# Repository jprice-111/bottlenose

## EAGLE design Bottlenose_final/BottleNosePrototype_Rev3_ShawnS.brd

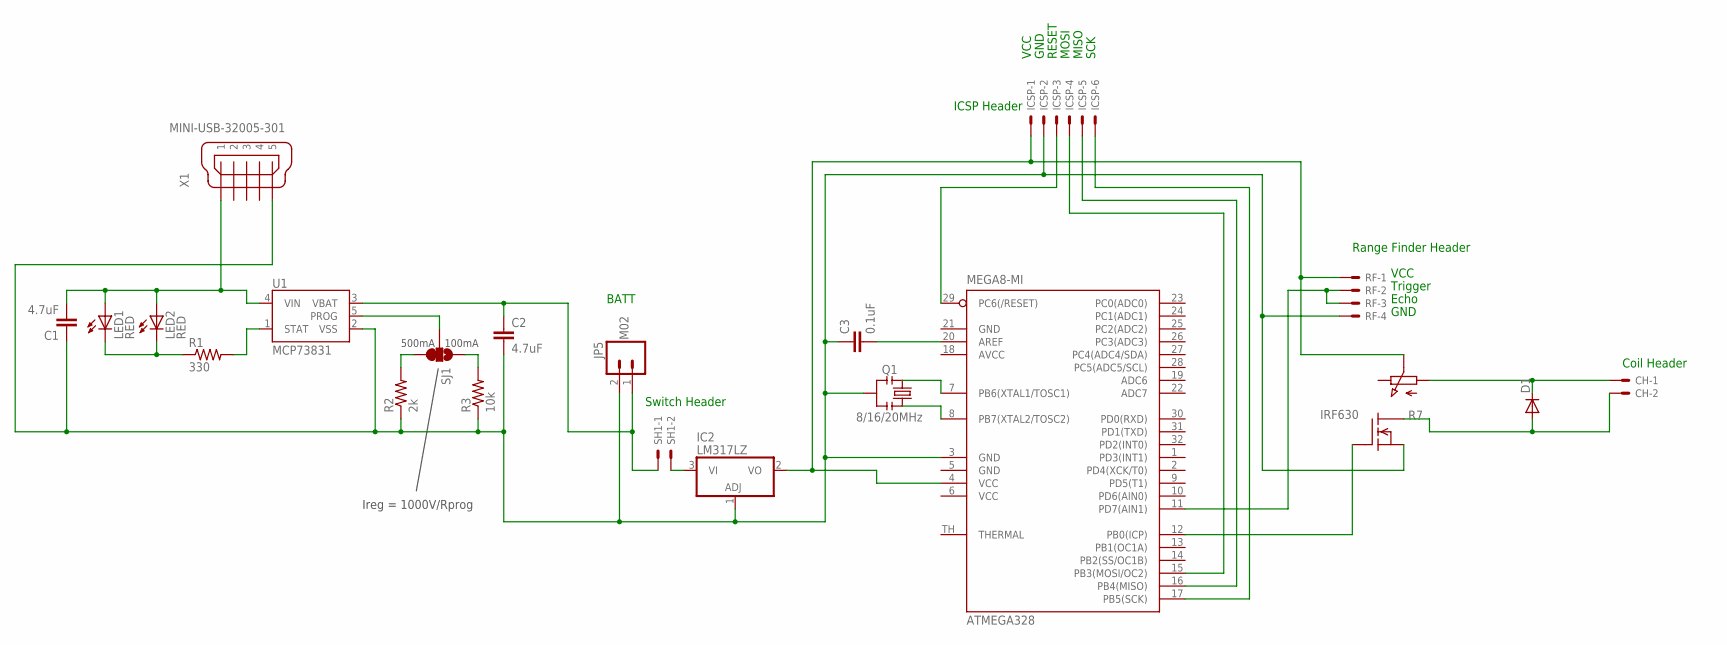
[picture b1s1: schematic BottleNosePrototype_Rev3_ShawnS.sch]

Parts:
ATMEGA328: MEGA8-MI; MLF32-TH; MPN ATMEGA88PA-MU
C1, C2: 4.7uF; 0402-CAP
C3: 0.1uF; 0402-CAP
CH: 22-23-2021
D1: DIODE-MICROMELF-R; MICROMELF-R
IC2: LM317LZ; TO92
ICSP: 22-23-2061
IRF630: IRF620; TO220
JP5: M02; 1X02
LED1, LED2: RED; LED-0603
Q1: 8/16/20MHz; RESONATOR-SMD
R1: 330; 0402-RES
R2: 2k; 0402-RES
R3: 10k; 0402-RES
R7: PC25
RF: 22-23-2041
SH1: 22-23-2021
SJ1: SOLDERJUMPER_2WAYS; SJ_3
U1: MCP73831; SOT23-5
X1: MINI-USB-32005-301; 32005-301

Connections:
AREF: ATMEGA328.20 (AREF), C3.2
AVCC: ATMEGA328.18 (AVCC)
GND: ATMEGA328.5 (GND), ATMEGA328.21 (GND)
unnamed: ATMEGA328.12 (PB0(ICP)), IRF630.1 (G)
unnamed: R1.2, U1.1 (STAT)
unnamed: LED1.C, LED2.C, R1.1
unnamed: R2.2, SJ1.3
unnamed: IC2.3 (VI), SH1.2
unnamed: CH.2, D1.A, IRF630.2 (D)
unnamed: R3.2, SJ1.1
unnamed: ATMEGA328.7 (PB6(XTAL1/TOSC1)), Q1.3
unnamed: ATMEGA328.8 (PB7(XTAL2/TOSC2)), Q1.1
unnamed: CH.1, D1.C, R7.A
unnamed: ATMEGA328.15 (PB3(MOSI/OC2)), ICSP.4
unnamed: ATMEGA328.17 (PB5(SCK)), ICSP.6
unnamed: ATMEGA328.16 (PB4(MISO)), ICSP.5
unnamed: ATMEGA328.29 (PC6(/RESET)), ICSP.3
unnamed: C1.2, LED1.A, LED2.A, U1.4 (VIN), X1.1
unnamed: C2.1, JP5.1, SH1.1, U1.3 (VBAT)
unnamed: ATMEGA328.3 (GND), C1.1, C2.2, C3.1, IC2.1 (ADJ), ICSP.2, IRF630.3 (S), JP5.2, Q1.2, R2.1, R3.1, RF.4, U1.2 (VSS), X1.5
unnamed: ATMEGA328.4 (VCC), IC2.2 (VO), ICSP.1, R7.S, RF.1
unnamed: ATMEGA328.11 (PD7(AIN1)), RF.2, RF.3
PROG: SJ1.2, U1.5 (PROG)
VCC: ATMEGA328.6 (VCC)

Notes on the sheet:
500mA
100mA
Ireg = 1000V/Rprog
VCC
Trigger
Echo
GND
Range Finder Header
Coil Header
Switch Header
RESET
MOSI
MISO
SCK
ICSP Header
BATT

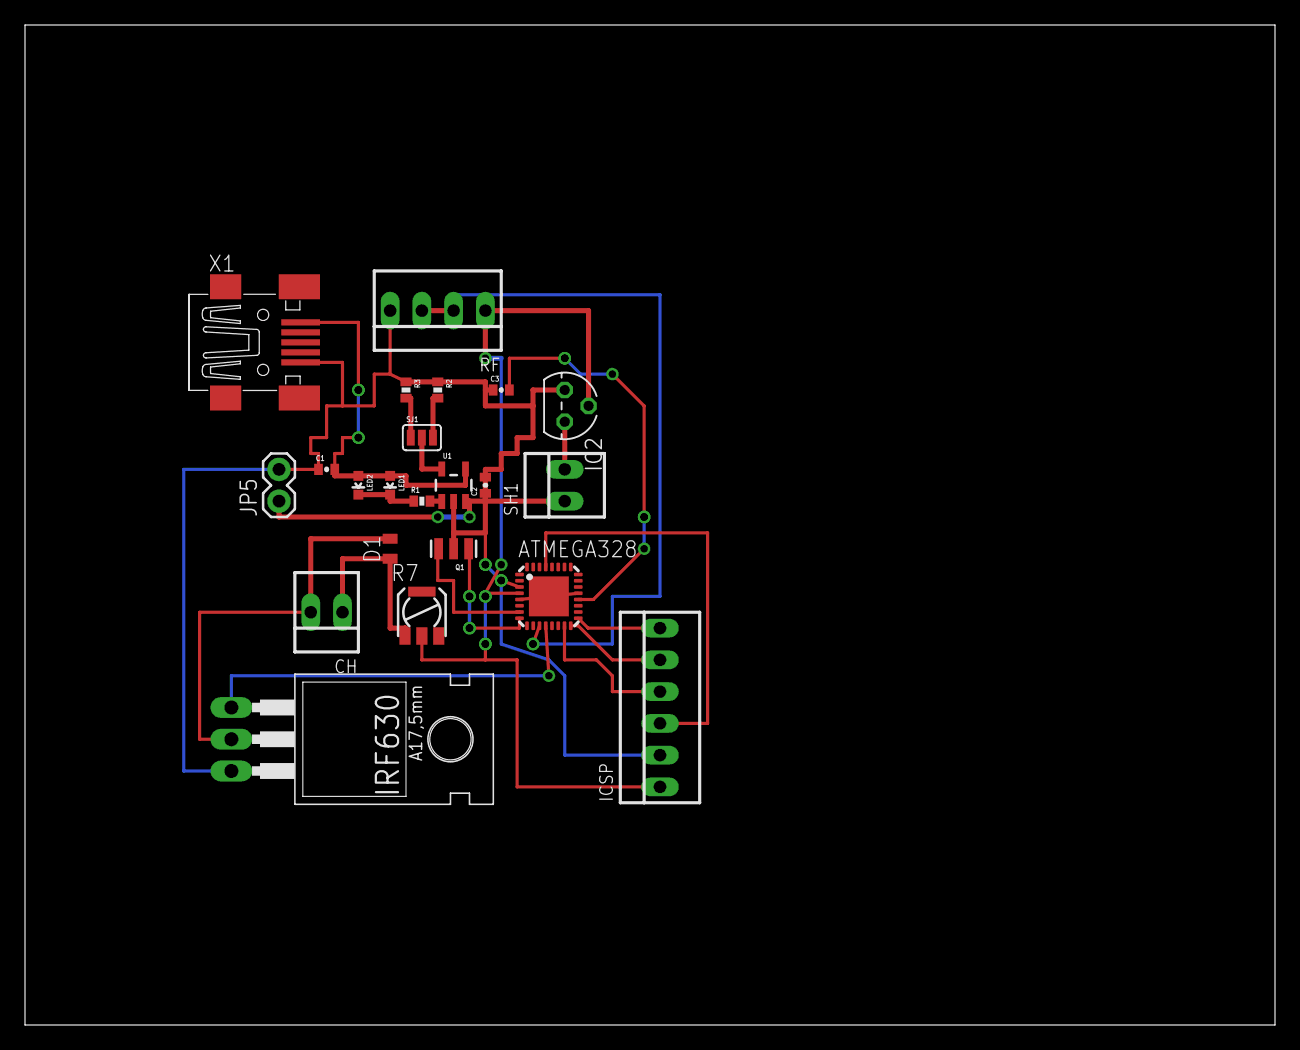
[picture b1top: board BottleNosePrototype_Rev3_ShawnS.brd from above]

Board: 2 copper layers, 100.0 x 80.0 mm, 22 parts (0 on the bottom side), 22 nets.

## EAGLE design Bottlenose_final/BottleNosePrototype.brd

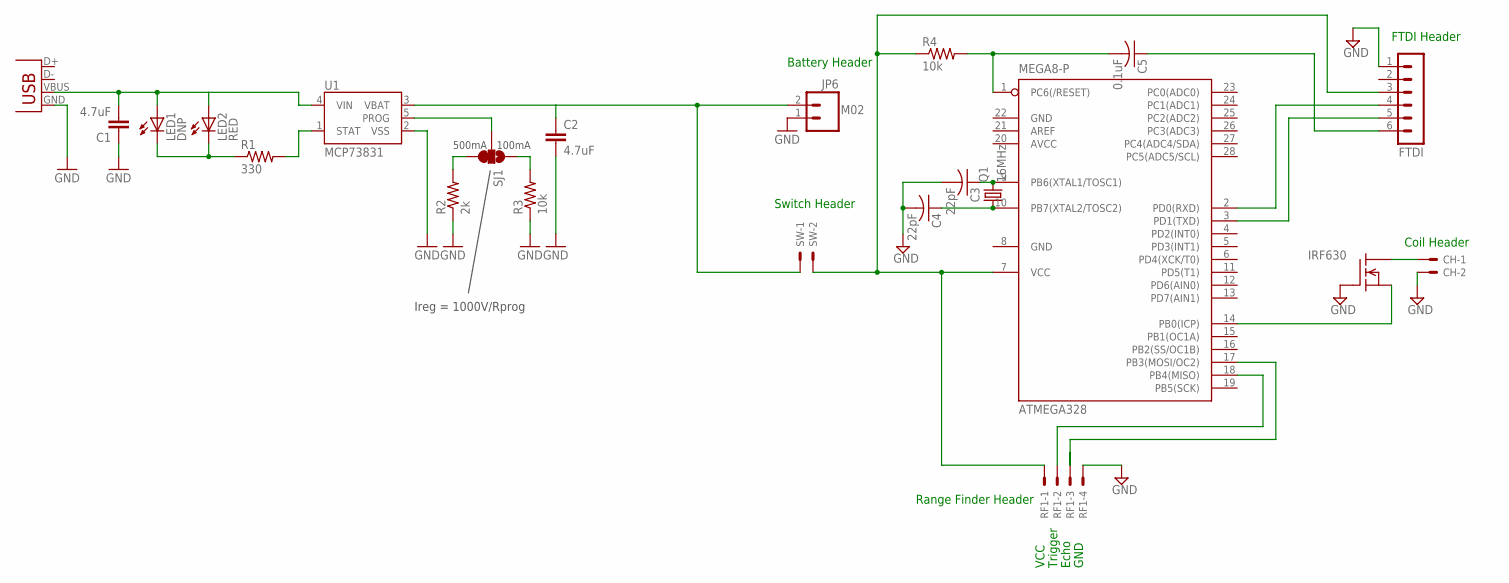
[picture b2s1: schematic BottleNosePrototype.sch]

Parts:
ATMEGA328: MEGA8-P; DIL28-3
C1, C2: 4.7uF; 0402-CAP
C3, C4: 22pF; C025-024X044
C5: 0.1uF; C025-024X044
CH: 22-23-2021
FTDI: MA06-1
IRF630: IRF620; TO220
JP6: M02; 1X02
LED1: DNP; LED3MM
LED2: RED; LED-0603
Q1: 16MHz; TC26V
R1: 330; 0402-RES
R2: 2k; 0402-RES
R3: 10k; 0402-RES
R4: 10k; 0204/5
RF1: 22-23-2041
SJ1: SOLDERJUMPER_2WAYS; SJ_3
SW: 22-23-2021
U1: MCP73831; SOT23-5
X2: USBSMD; USB-MINIB

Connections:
AVCC: ATMEGA328.20 (AVCC)
GND: ATMEGA328.8 (GND), ATMEGA328.22 (GND), C1.1, C2.2, C3.2, C4.2, CH.2, FTDI.1, IRF630.1 (G), JP6.1, R2.1, R3.1, RF1.4, U1.2 (VSS), X2.GND
unnamed: R1.2, U1.1 (STAT)
unnamed: LED1.K (C), LED2.C, R1.1
unnamed: R2.2, SJ1.3
unnamed: ATMEGA328.7 (VCC), FTDI.3, R4.1, RF1.1, SW.2
unnamed: C2.1, JP6.2, SW.1, U1.3 (VBAT)
unnamed: R3.2, SJ1.1
unnamed: ATMEGA328.9 (PB6(XTAL1/TOSC1)), C3.1, Q1.2
unnamed: ATMEGA328.18 (PB4(MISO)), RF1.2
unnamed: ATMEGA328.14 (PB0(ICP)), IRF630.3 (S)
unnamed: CH.1, IRF630.2 (D)
unnamed: ATMEGA328.10 (PB7(XTAL2/TOSC2)), C4.1, Q1.1
unnamed: ATMEGA328.17 (PB3(MOSI/OC2)), RF1.3
unnamed: ATMEGA328.2 (PD0(RXD)), FTDI.4
unnamed: ATMEGA328.3 (PD1(TXD)), FTDI.5
unnamed: C5.1, FTDI.6
unnamed: ATMEGA328.1 (PC6(/RESET)), C5.2, R4.2
unnamed: C1.2, LED1.A, LED2.A, U1.4 (VIN), X2.VBUS
PROG: SJ1.2, U1.5 (PROG)

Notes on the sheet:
500mA
100mA
Ireg = 1000V/Rprog
Range Finder Header
Coil Header
VCC
Trigger
Echo
GND
Switch Header
Battery Header
FTDI Header

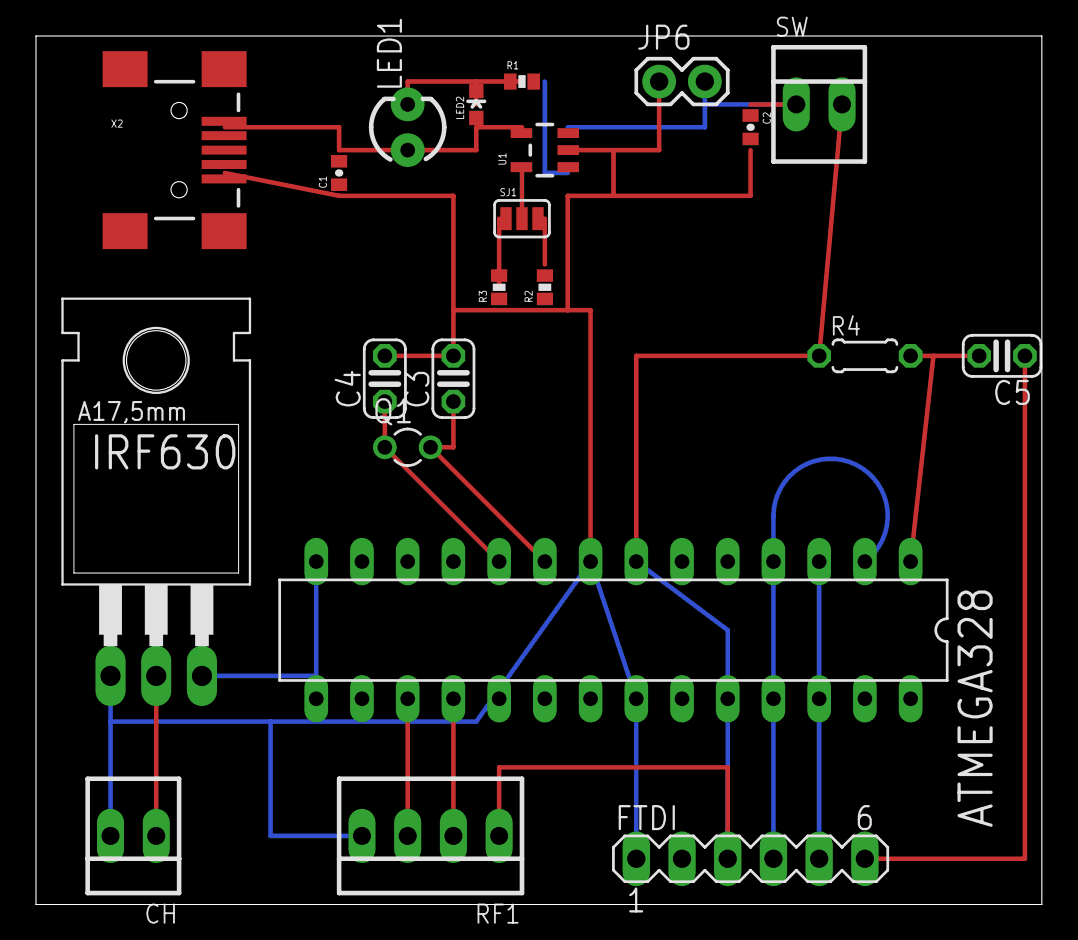
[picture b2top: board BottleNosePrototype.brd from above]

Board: 2 copper layers, 55.9 x 48.2 mm, 22 parts (0 on the bottom side), 19 nets.

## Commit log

2013-02-01 by Marlo, 1/2/2013, to incorporate thermosensor.
2013-03-18 Mike's current code
2013-03-18 libraries
2013-03-31 using this to make a directory.
2013-03-31 A custom eagle library containing the battery charger IC and the thermosensor.
2013-03-31 An updated copy of the bottlenose eagle schematic.
2013-03-31 An updated copy of the bottlenose arduino sketch. Shouldn't suffer from lag, notify me if it does. Relies on an external switch to change between sensors (pin 9 or pin 10 high).
2013-03-31 Pictures of a mock setup of an electromagnet. Not sure if it's the best possible way, but this is how I imagined it.
2013-03-31 Parts list. Content will end up in the google docs copy.
2013-03-31 attempted to fix broken rtf encoding by pasting in regular text
2013-04-20 Update with miker's new stuff.
2013-04-22 Sent today by Lucas, checked in for safe-keeping
2013-04-24 Made a change for my first commit to svn
2013-04-24 Training in SVN for Shawn.
2013-04-24 I have removed the previous .sch file and replaced it with a more current .sch file. The current .sch now illustrates how the Pittsburgh prototype is constructed.
2013-04-29 added a license and some comments
2013-04-30 I have modified the Bottlenose_final/BottleNosePrototype.sch to add FTDI header and add crystal filter, the charging circuit was modified for our needs.
2013-05-01 Changes to .sch were to add ftdi header to bottleNosePrototype. The addition of the BottleNosePrototype.brd which is made from the previous .sch.
2013-05-01 Modified .sch, made it so that all GND symbols were the same.
2013-05-01 I have added dimensions to the .brd file.
2013-05-01 There was a value error on a couple of connections
2013-05-01 There was a couple of value errors
2013-05-13 A schematic that Shawn and I are both happy with.
2013-05-15 added flyback diode and changed MOSFET wiring.
2013-05-15 added flyback diode and changed mosfet wiring. also, moved trim pot to coil line, mikers idea.
2013-05-18 Removed switch from the .sch and replaced it with a switch header.
2013-05-21 Just cleaning up the .sch file
2013-06-12 Found missing junction. Put junction in proper area. That is the only change to the .sch file.
2013-06-30 Add JoeRoganBottleNose.ino to SVN, for the Joe Rogan show.
2013-07-07 Modified the .sch to meet current and only working build of bottlenose.
2013-07-10 Added new bottlenose .sch and .brd files to svn. They are labeled BottleNosePrototype_Rev3_ShawnS.sch and BottleNosePrototype_Rev3_ShawnS.brd.
2013-07-10 added and finished new files for bottlenose.
2013-07-10 removed redundant files
2016-02-25 Migrating wiki contents from Google Code
